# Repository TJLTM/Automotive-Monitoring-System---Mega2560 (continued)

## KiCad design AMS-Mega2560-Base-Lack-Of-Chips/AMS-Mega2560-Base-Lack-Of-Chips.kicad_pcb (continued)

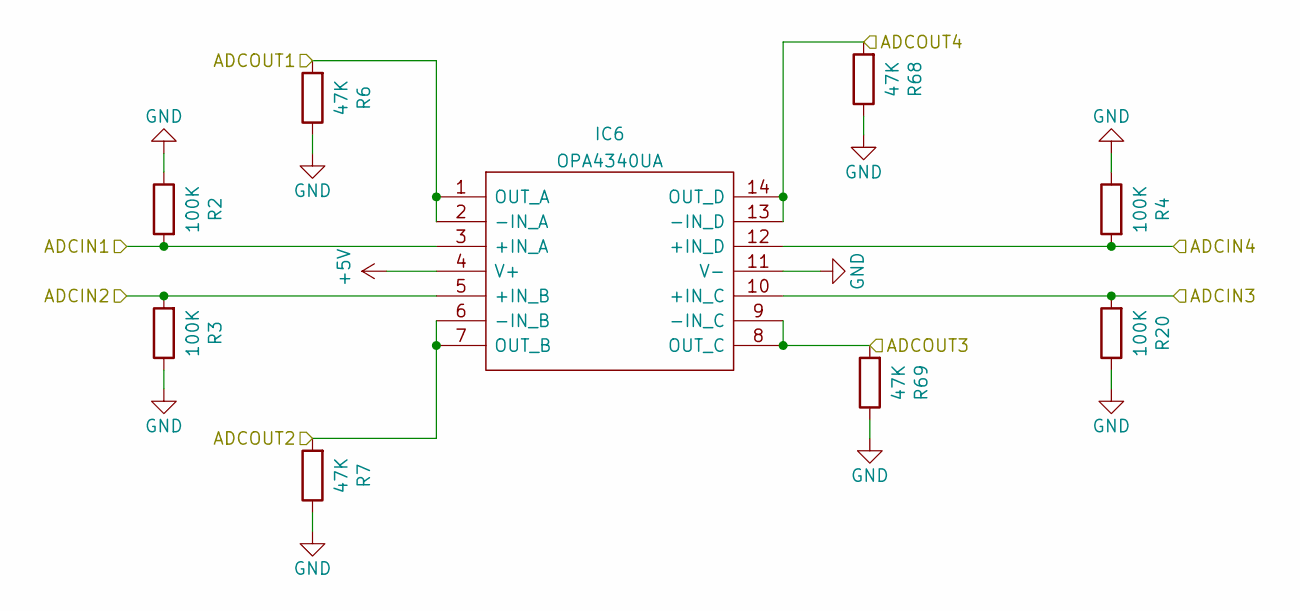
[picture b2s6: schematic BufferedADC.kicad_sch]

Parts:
IC6: OPA4340UA; SOIC127P600X175-14N; Mouser Part Number 595-OPA4340UA
R2, R3, R4, R20: 100K; R_Axial_DIN0207_L6.3mm_D2.5mm_P2.54mm_Vertical
R6, R7, R68, R69: 47K; R_Axial_DIN0207_L6.3mm_D2.5mm_P2.54mm_Vertical

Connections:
AFR1: IC6.6 (-IN_B), IC6.7 (OUT_B), R7.2; also elsewhere on the board
AFR2: IC6.8 (OUT_C), IC6.9 (-IN_C), R69.2; also elsewhere on the board
AltCurrent: IC6.13 (-IN_D), IC6.14 (OUT_D), R68.2; also elsewhere on the board
OilPressure: IC6.1 (OUT_A), IC6.2 (-IN_A), R6.2; also elsewhere on the board

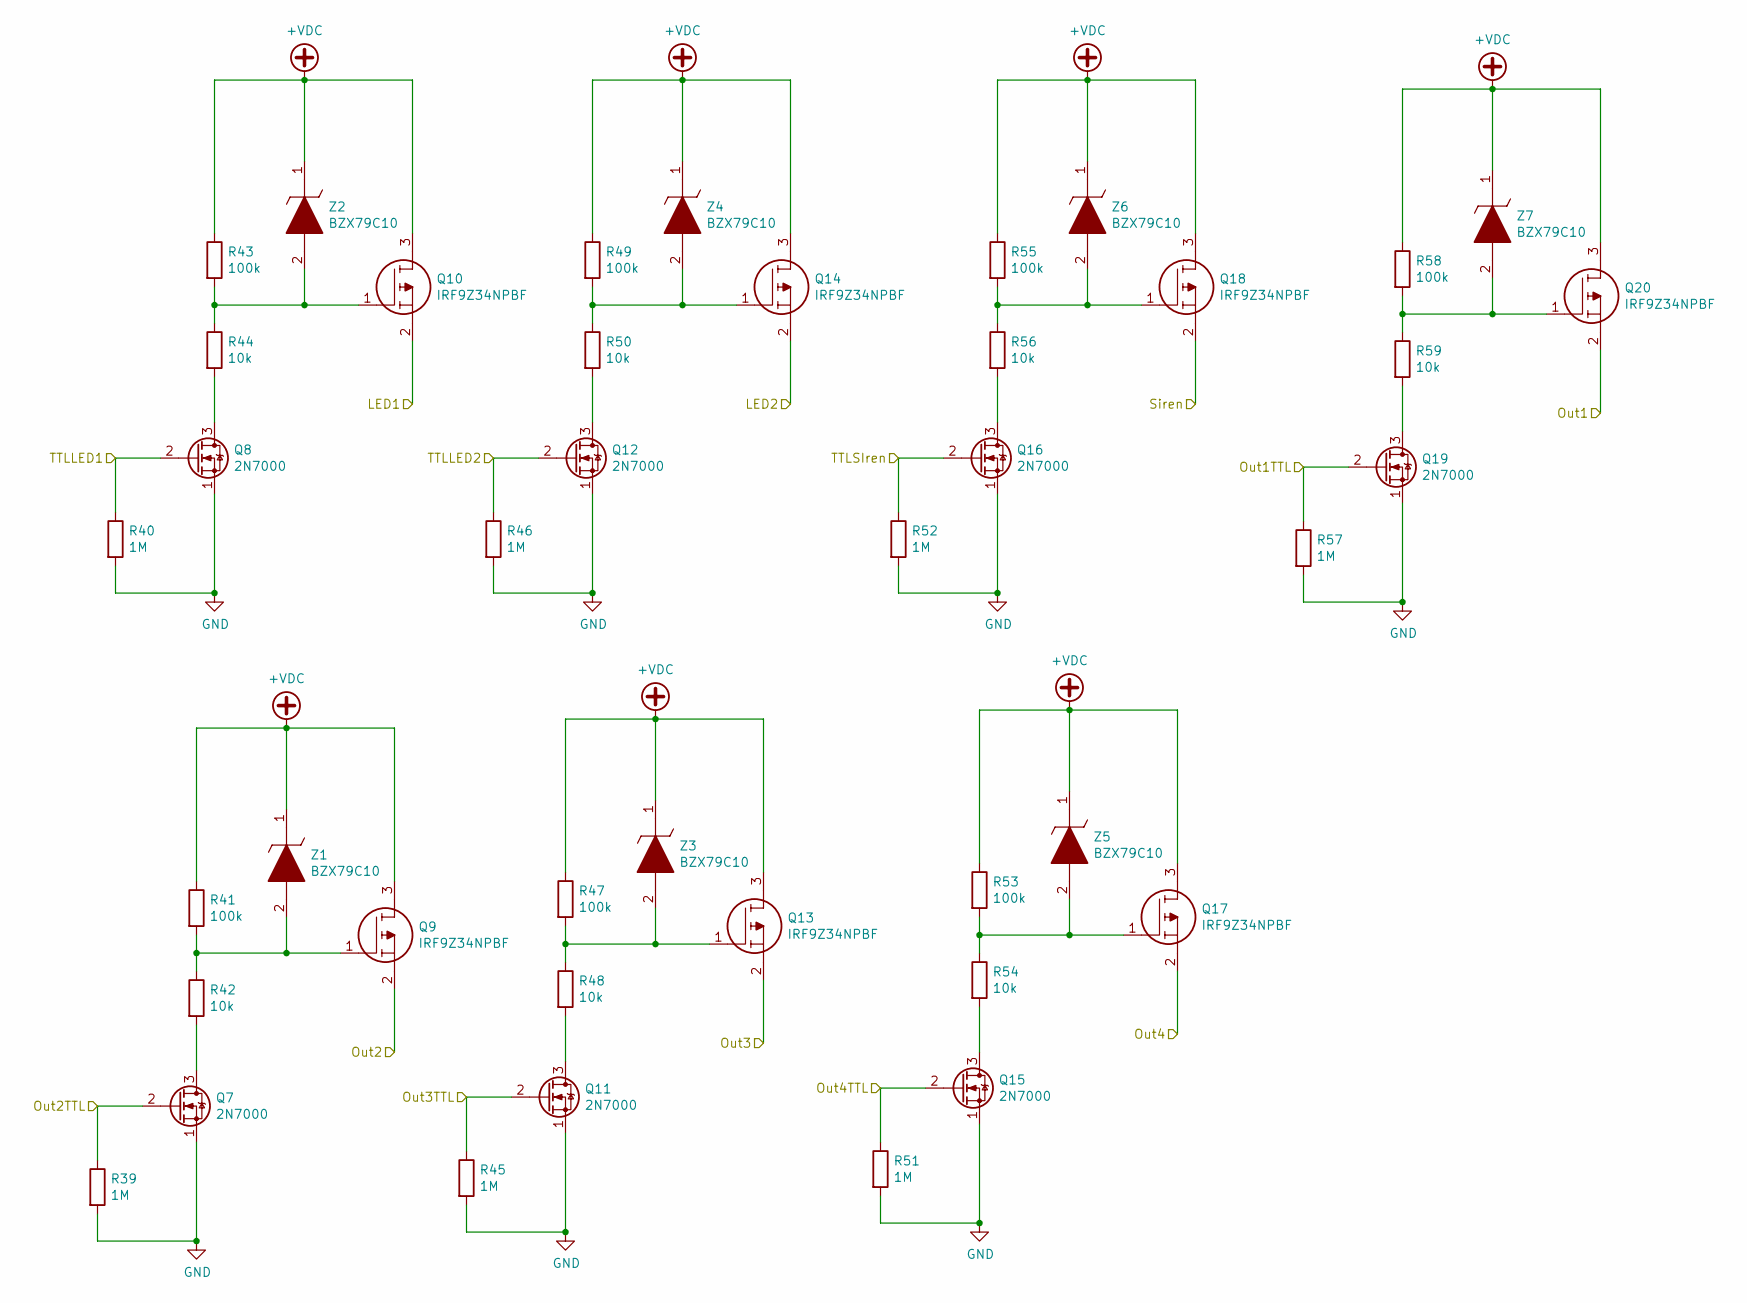
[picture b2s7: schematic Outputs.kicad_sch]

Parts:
Q7, Q8, Q11, Q12, Q15, Q16, Q19: 2N7000; TO-92_Inline
Q9, Q10, Q13, Q14, Q17, Q18, Q20: IRF9Z34NPBF; TO254P469X1042X1967-3P; Mouser Part Number 942-IRF9Z34NPBF
R39, R40, R45, R46, R51, R52, R57: 1M; R_Axial_DIN0207_L6.3mm_D2.5mm_P2.54mm_Vertical
R41, R43, R47, R49, R53, R55, R58: 100k; R_Axial_DIN0207_L6.3mm_D2.5mm_P2.54mm_Vertical
R42, R44, R48, R50, R54, R56, R59: 10k; R_Axial_DIN0207_L6.3mm_D2.5mm_P2.54mm_Vertical
Z1, Z2, Z3, Z4, Z5, Z6, Z7: BZX79C10; DIOAD1068W53L380D172; Mouser Part Number 512-BZX79C10

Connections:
+VDC: Q9.3, Q10.3, Q13.3, Q14.3, Q17.3, Q18.3, Q20.3, R41.1, R43.1, R47.1, R49.1, R53.1, R55.1, R58.1, Z1.1, Z2.1, Z3.1, Z4.1, Z5.1, Z6.1, Z7.1; also elsewhere on the board
unnamed: Q7.3 (D), R42.2
unnamed: Q8.3 (D), R44.2
unnamed: Q9.1, R41.2, R42.1, Z1.2
unnamed: Q10.1, R43.2, R44.1, Z2.2
unnamed: Q11.3 (D), R48.2
unnamed: Q12.3 (D), R50.2
unnamed: Q13.1, R47.2, R48.1, Z3.2
unnamed: Q14.1, R49.2, R50.1, Z4.2
unnamed: Q15.3 (D), R54.2
unnamed: Q16.3 (D), R56.2
unnamed: Q17.1, R53.2, R54.1, Z5.2
unnamed: Q18.1, R55.2, R56.1, Z6.2
unnamed: Q19.3 (D), R59.2
unnamed: Q20.1, R58.2, R59.1, Z7.2
OUTPUT1: Q19.2 (G), R57.1; also elsewhere on the board
OUTPUT2: Q7.2 (G), R39.1; also elsewhere on the board
OUTPUT3: Q11.2 (G), R45.1; also elsewhere on the board
OUTPUT4: Q15.2 (G), R51.1; also elsewhere on the board
OUTPUTLED1: Q8.2 (G), R40.1; also elsewhere on the board
OUTPUTLED2: Q12.2 (G), R46.1; also elsewhere on the board
OUTPUTSiren: Q16.2 (G), R52.1; also elsewhere on the board
Sense2-3: Q20.2; also elsewhere on the board
Sense2-5: Q18.2; also elsewhere on the board
Sense2-6: Q9.2; also elsewhere on the board
Sense2-8: Q14.2; also elsewhere on the board
Sense2-9: Q13.2; also elsewhere on the board
Sense2-11: Q10.2; also elsewhere on the board
Sense2-12: Q17.2; also elsewhere on the board

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
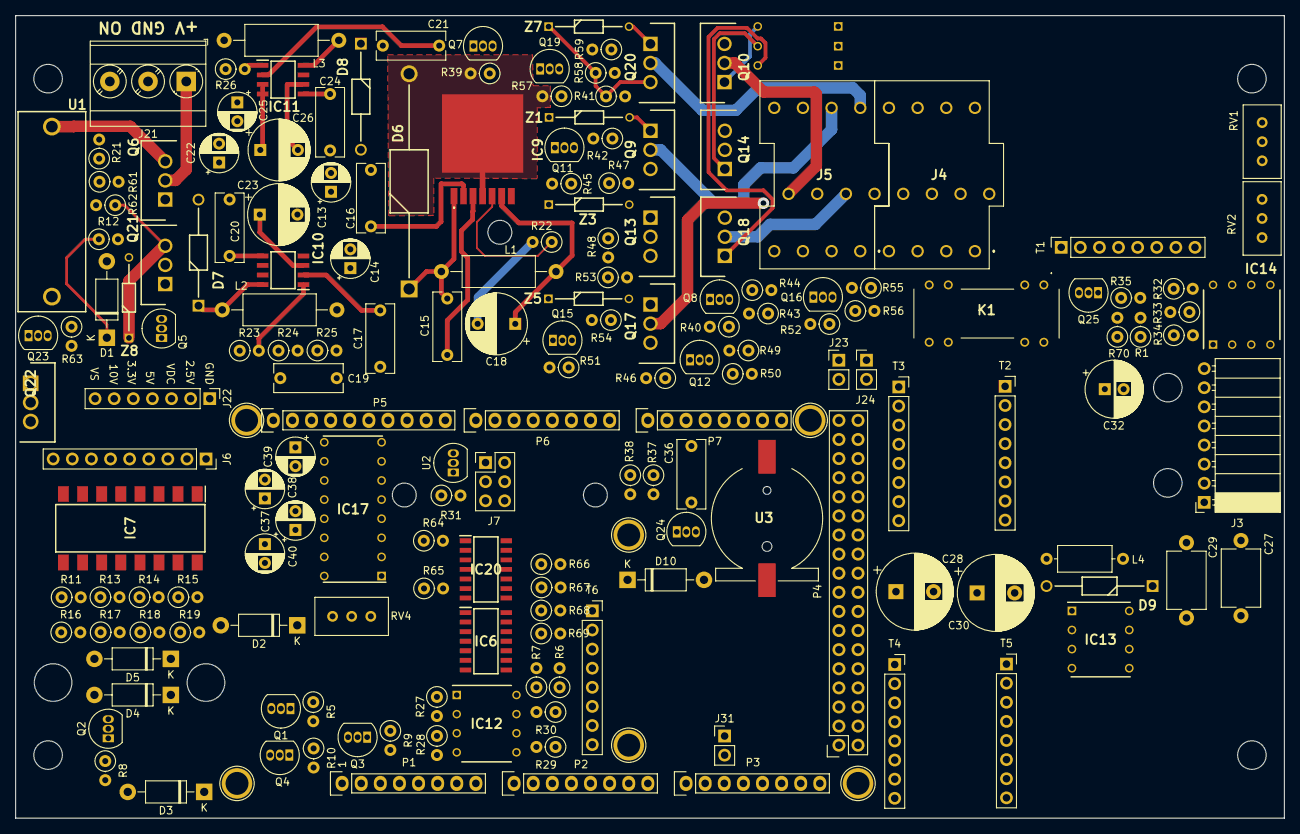
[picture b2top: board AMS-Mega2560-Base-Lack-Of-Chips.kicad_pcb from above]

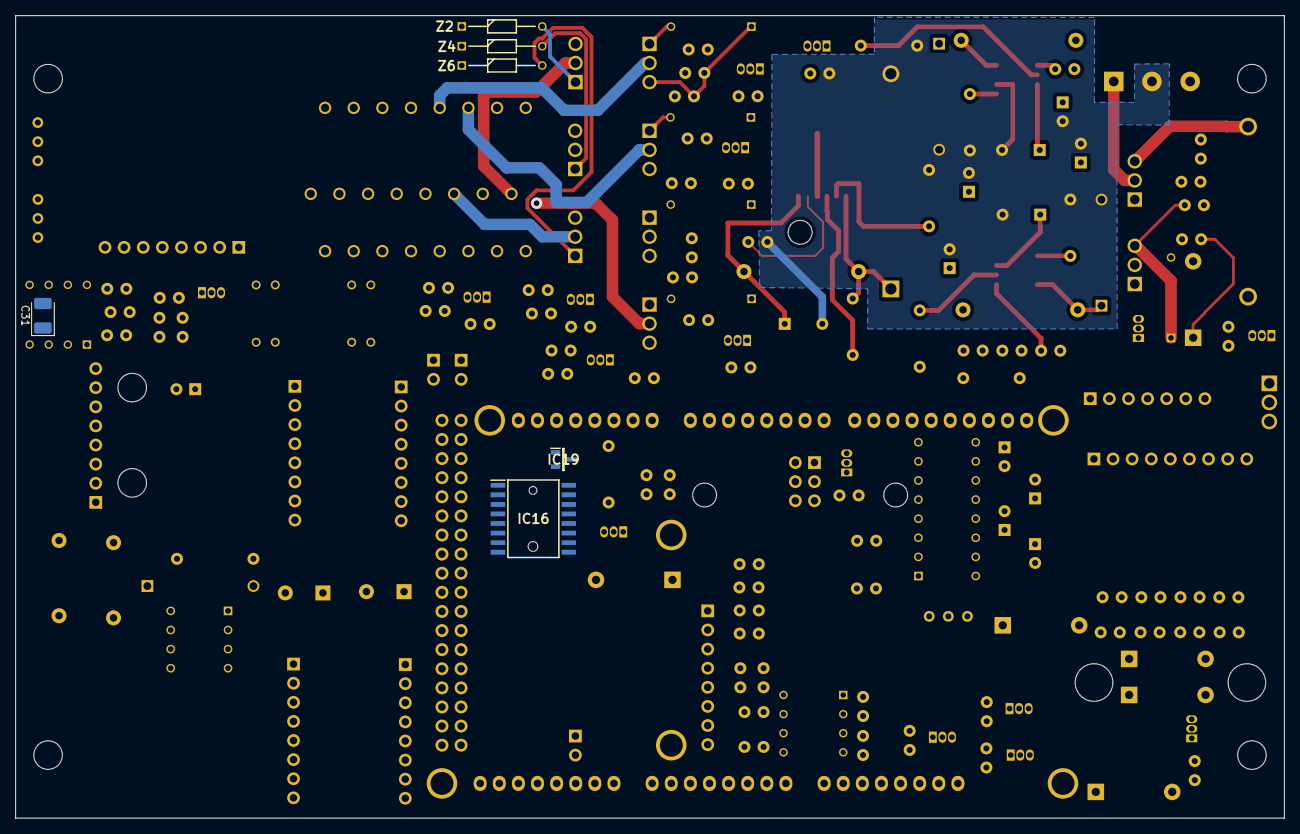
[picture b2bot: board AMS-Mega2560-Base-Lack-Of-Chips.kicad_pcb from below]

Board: 4 copper layers, 168.7 x 106.7 mm, 184 parts (6 on the bottom side), 141 nets.

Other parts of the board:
C36: 0.1uF; C_Rect_L9.0mm_W3.6mm_P7.50mm_MKT
D10: 1N4001; D_DO-41_SOD81_P10.16mm_Horizontal
IC16: DS3231SN#; SOIC127P1032X265-16N
IC19: MAX6326UR31+T; SOT95P237X112-3N
IC20: OPA4340UA; SOIC127P600X175-14N
Q24: BS250; TO-92_Inline
R37, R38: 10k; R_Axial_DIN0207_L6.3mm_D2.5mm_P2.54mm_Vertical
R64, R65, R66, R67: 47K; R_Axial_DIN0207_L6.3mm_D2.5mm_P2.54mm_Vertical
U3: S8411-45R; S8411-45R_1

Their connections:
/A1: Q24.1 (D), U3.1 (+); also elsewhere on the board
/BufferedADC/ADCIN4: IC20.12 (+IN_D); also elsewhere on the board
FuelPressure1: IC20.1 (OUT_A), IC20.2 (-IN_A), R64.2; also elsewhere on the board
FuelPressure2: IC20.6 (-IN_B), IC20.7 (OUT_B), R65.2; also elsewhere on the board
unnamed: D10.1 (K), IC16.14 (VBAT), Q24.3 (S)
unnamed: IC19.2 (~RESET), Q24.2 (G)
SCL: IC16.16 (SCL), R37.2; also elsewhere on the board
SDA: IC16.15 (SDA), R38.2; also elsewhere on the board
Sense1-6: IC20.10 (+IN_C); also elsewhere on the board
Sense1-9: IC20.5 (+IN_B); also elsewhere on the board
Sense1-12: IC20.3 (+IN_A); also elsewhere on the board
SpareBufferedADC: IC20.13 (-IN_D), IC20.14 (OUT_D), R66.2; also elsewhere on the board
ThrottlePositionADC: IC20.8 (OUT_C), IC20.9 (-IN_C), R67.2; also elsewhere on the board

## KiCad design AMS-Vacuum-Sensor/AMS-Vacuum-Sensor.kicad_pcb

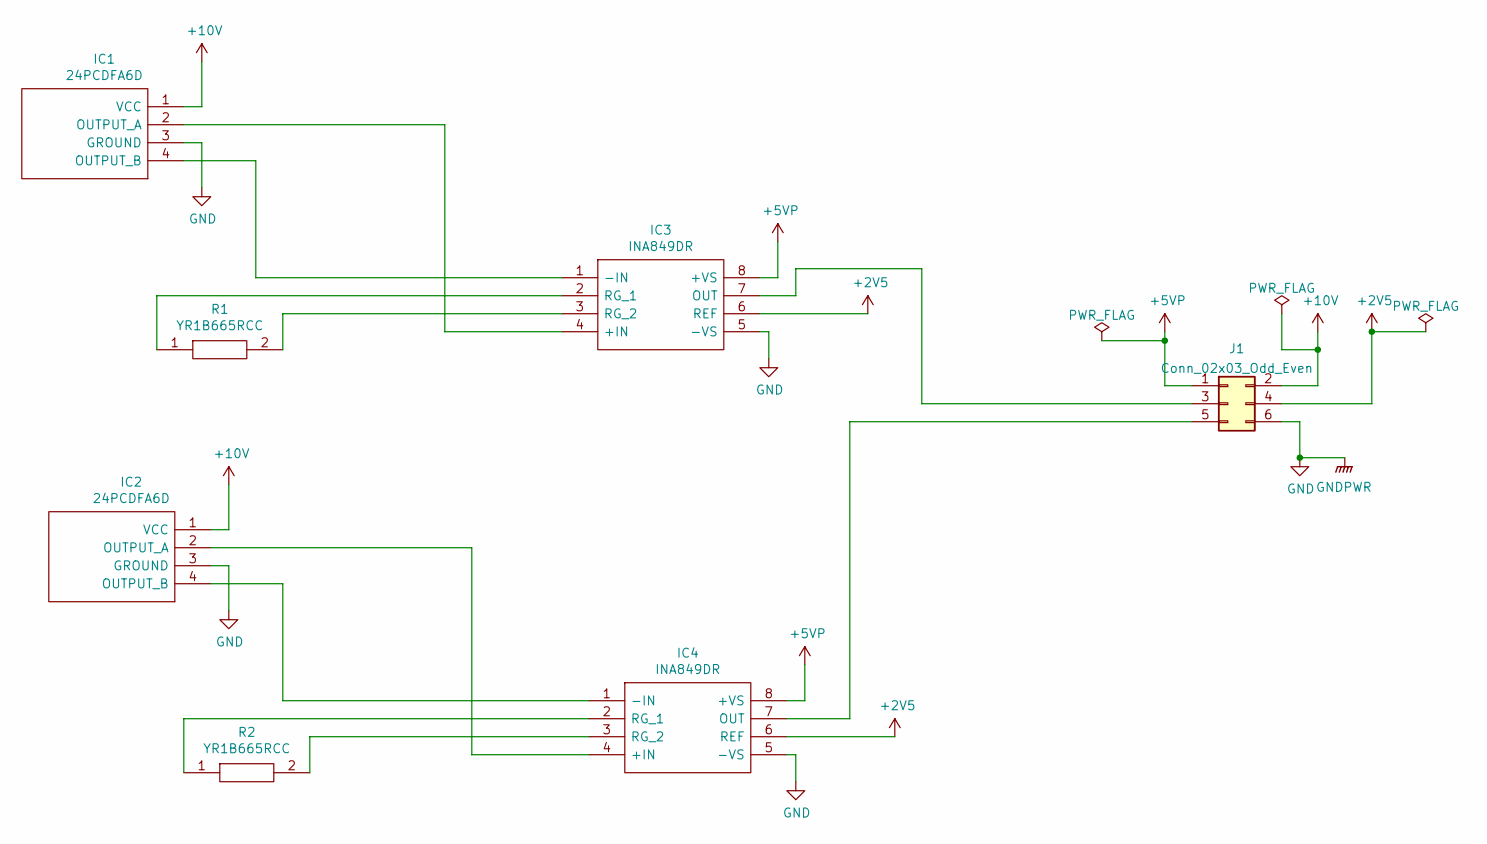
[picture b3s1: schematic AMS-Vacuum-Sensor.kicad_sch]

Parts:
IC1, IC2: 24PCDFA6D; Mouser Part Number 785-24PCDFA6D
IC3, IC4: INA849DR; SOIC127P600X175-8N; Mouser Part Number 595-INA849DR
J1: Conn_02x03_Odd_Even; PinHeader_2x03_P2.54mm_Vertical
R1, R2: YR1B665RCC; RESAD1550W60L630D230; Mouser Part Number 279-YR1B665RCC

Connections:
+2V5: IC3.6 (REF), IC4.6 (REF), J1.4
+5VP: IC3.8 (+VS), IC4.8 (+VS), J1.1
+10V: IC1.1 (VCC), IC2.1 (VCC), J1.2
GND: IC1.3 (GROUND), IC2.3 (GROUND), IC3.5 (-VS), IC4.5 (-VS), J1.6
unnamed: IC1.2 (OUTPUT_A), IC3.4 (+IN)
unnamed: IC1.4 (OUTPUT_B), IC3.1 (-IN)
unnamed: IC2.2 (OUTPUT_A), IC4.4 (+IN)
unnamed: IC2.4 (OUTPUT_B), IC4.1 (-IN)
unnamed: IC3.2 (RG_1), R1.1
unnamed: IC3.3 (RG_2), R1.2
unnamed: IC3.7 (OUT), J1.3
unnamed: IC4.2 (RG_1), R2.1
unnamed: IC4.3 (RG_2), R2.2
unnamed: IC4.7 (OUT), J1.5

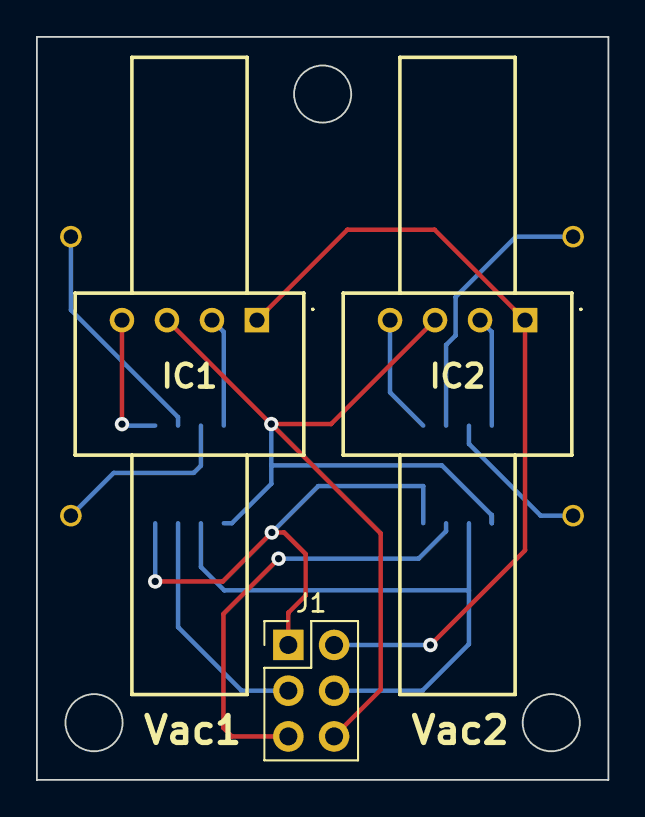
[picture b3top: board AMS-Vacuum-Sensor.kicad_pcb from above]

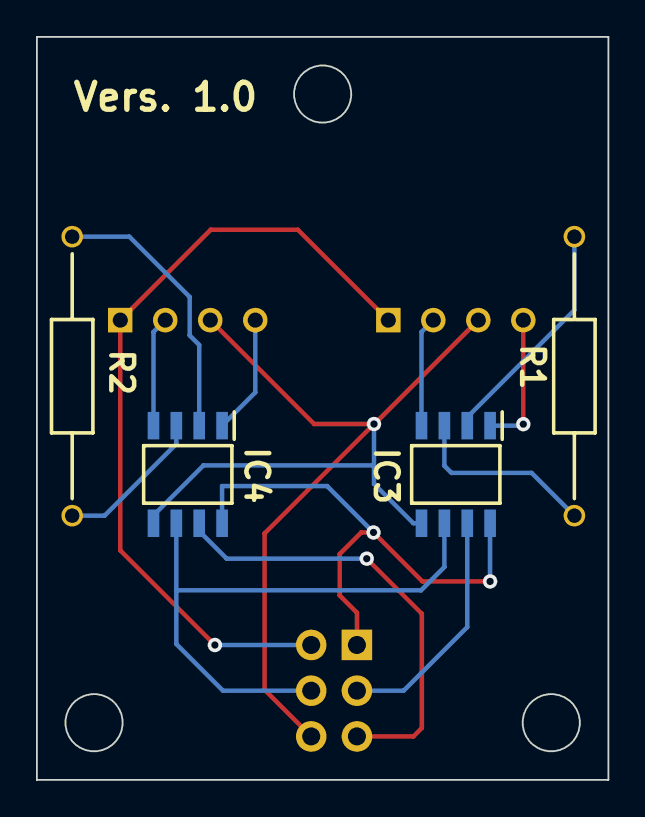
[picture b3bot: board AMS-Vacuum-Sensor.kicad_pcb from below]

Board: 2 copper layers, 31.8 x 41.3 mm, 7 parts (4 on the bottom side), 14 nets.

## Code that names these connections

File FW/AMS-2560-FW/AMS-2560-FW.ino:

#include <LiquidCrystal_I2C.h>
#include <Wire.h>
#include <Adafruit_MAX31865.h>
#include <SPI.h>
#include <RTClib.h>
#include <EEPROM.h>

//-----------------------------------------------------------
// Serial Communication, UI 
//-----------------------------------------------------------
#define USBSerial Serial
#define RS232 Serial2
#define GPSSerial Serial3
String inputString, inputStringRS232 = "";         // a String to hold incoming data from ports
bool stringComplete, stringCompleteRS232 = false;     // whether the string is complete for each respective port

char* AcceptedCommands[] = {"UNITS?", "DEVICE?", "BATTERY?", "RTCBATTERY?", "TEMPS?", "UNITTEMP?", "WARNING?",
                            "STREAMING?", "ALLDATA?", "UPDATEALL", "RESETWARNINGS", "RESETALLALARMS",
                            "TIME?", "REBOOT", "RESET", "STREAMINGONBOOT?"
                           };
char* ParameterCommands[] = {"SETUNITS", "SETSTREAMINGDATA", "SETOUTPUT", "READINPUT", "SETTIME", "GETOUTPUT", "READANALOG", 
                             "SETSTREAMINGONBOOT"
                            };

//-----------------------------------------------------------
// System Level
RTC_DS3231 rtc;
const String DeviceName = "AMS";
const String FWVersion = "1.0.0";
const float ConversionFactor = 5.0 / 1023;

char Units;
String TempUnits, PressureUnits;
const String StatesForOutput[2] = {"Off", "On"};

//-----------------------------------------------------------
//-----------------------------------------------------------
//Spare IO
/*
   Spare Inputs are indexed by their number +1 because I don't
   want to start at zero.
*/
const int SpareInputs[] = {2,3,47};
const int SpareInputSize = sizeof(SpareInputs) / sizeof(int);
int LastInputState[] = {};
const int SpareOutputs[] = {4,5,6,7};
const int SpareOutputSize = sizeof(SpareOutputs) / sizeof(int);
//-----------------------------------------------------------
//-----------------------------------------------------------
//Analog Sensors 
#define VoltageSensor A0
#define RTCBattery A1
#define Vacuum1 A2
#define Vacuum A3
#define AtlernatorCurrent A4
#define FuelPresssure1 A5
#define FuelPressure2 A6
#define AFR1 A8
#define AFR2 A9
#define RPM A10
#define GPSBattery A11
#define ThrottlePosition A12
#define SpareBufferedADC A13
//-----------------------------------------------------------
//-----------------------------------------------------------
//Specific IO 
#define OutputSiren 10
#define LED1 43
#define LED2 45
#define LoggingIn 49
#define SDCardDetect 34
//-----------------------------------------------------------
//-----------------------------------------------------------
//RTD 
#define RREF 430.0
#define RNOMINAL 100.0
#define RTDCLK 44
#define RTDDI 48
#define RTDDO 46
Adafruit_MAX31865 Water = Adafruit_MAX31865(48, RTDDI, RTDDO, RTDCLK);
Adafruit_MAX31865 LeftSide = Adafruit_MAX31865(46, RTDDI, RTDDO, RTDCLK);
Adafruit_MAX31865 RightSide = Adafruit_MAX31865(44, RTDDI, RTDDO, RTDCLK);
Adafruit_MAX31865 Carb = Adafruit_MAX31865(38, RTDDI, RTDDO, RTDCLK);
Adafruit_MAX31865 FrontOfEngine = Adafruit_MAX31865(42, RTDDI, RTDDO, RTDCLK);
Adafruit_MAX31865 Ambient = Adafruit_MAX31865(40, RTDDI, RTDDO, RTDCLK);
//-----------------------------------------------------------
//-----------------------------------------------------------
/*
   All the Stored Values and Times to have states
   that can be recalled if streaming is turned off
*/
//Energy Monitoring
float LastDCVoltage, LastAltCurrent, LastRTCVoltage = 0.0;
String LastTimeDCVoltage, LastTimeRTCVoltage = "";
//Temps
String LastTimeTemp = "";
float LastFrontACTemp, LastBackACTemp, LastOutsideTemp, LastBackCabinTemp, LastHallwayTemp, LastFreezerTemp, LastFridgeTemp,
      LastBathroomTemp = 0.0;
//RTC TEMP
float LastRTCTemp = 0.0;
String LastTimeRTCTemp = "";
//-----------------------------------------------------------
//-----------------------------------------------------------

void setup() {
  rtc.begin();
  RS232.begin(115200);
  USBSerial.begin(115200);
  inputString.reserve(200);
  inputStringRS232.reserve(200);

  for (int i = 0; i <= SpareInputSize; i++) {
    pinMode(SpareInputs[i], INPUT);
    LastInputState[i] = digitalRead(SpareInputs[i]);
  }
  for (int i = 0; i <= SpareOutputSize; i++) {
    pinMode(SpareOutputs[i], OUTPUT);
  }

}

void loop() {
  

}


//------------------------------------------------------------------
//Helper functions
//------------------------------------------------------------------
void(* resetFunc) (void) = 0;  // declare reset fuction at address 0

void RebootDisBitch() {
  BroadCast("%R," + GetCurrentTime() + ",Rebooting");
  delay(2000);
  resetFunc();
}

void MIBFLASH() {
  BroadCast("%R," + GetCurrentTime() + ",Reseting wait for reboot Message");
  for (int i = 0 ; i < EEPROM.length() ; i++) {
    EEPROM.write(i, 0);
  }
  RebootDisBitch();
}

float ConvertCtoF(float C) {
  float F = (1.8 * C) + 32;
  return F;
}

float ConvertPSItoKPa(float PSI) {
  float KPA = 6.8947572932 * PSI;
  return KPA;
}

String GetCurrentTime() {
  DateTime now = rtc.now();

  char buf1[20];
  sprintf(buf1, "%02d:%02d:%02d-%02d/%02d/%02d",  now.hour(), now.minute(), now.second(), now.day(), now.month(), now.year());
  LastTimeRTCTemp = buf1;
  
  if (Units == 'I') {
    LastRTCTemp = ConvertCtoF(rtc.getTemperature());
  }
  else {
    LastRTCTemp = rtc.getTemperature();
  }
  return DateTimeString;
}

String GetCurrentDate() {
  DateTime now = rtc.now();
  String CurrentDate = String(now.year()) + String(now.month()) + String(now.day());
  return CurrentDate;
}

void SetUnitsForOutput() {
  if (Units == "M") {
    TempUnits = "C";
    PressureUnits = "KPa";
  }
  else {
    TempUnits = "F";
    PressureUnits = "PSI";
  }
}

void ReadAllInputs() {
  for (int i = 1; i <= SpareInputSize; i++) {
    int CurrentInputRead = ReadInput(SpareInputs[i]);
    if (CurrentInputRead != LastInputState[i]) {
      LastInputState[i] = CurrentInputRead;
      if (StreamingDataUSB == true) {
        PrintInputState(i, CurrentInputRead, 0);
      }
      if (StreamingDataRS232 == true) {
        PrintInputState(i, CurrentInputRead, 1);
      }

    }
  }
}

int ReadInput(int Number) {
  int Value = digitalRead(SpareInputs[Number]);
  return Value;
}

int ReadOutput(int Number) {
  int Value = digitalRead(SpareOutputs[Number - 1]);
  return Value;
}

float ReadAnalog(int Samples, int PinNumber) {
  long Sum = 0;
  float Value = 0;
  for (int x = 0; x < Samples; x++) {
    Sum = Sum + analogRead(PinNumber);
  }
  Value = (Sum / Samples);
  return Value;
}


//------------------------------------------------------------------
//Serial
//------------------------------------------------------------------
/*
  SerialEvent occurs whenever a new data comes in the hardware serial RX. This
  routine is run between each time loop() runs, so using delay inside loop can
  delay response. Multiple bytes of data may be available.
*/
void serialEvent() {
  while (USBSerial.available()) {
    // get the new byte:
    char inChar = (char)USBSerial.read();
    // add it to the inputString:
    inputString += inChar;
    // if the incoming character is a carriage return, set a flag so the main loop can
    // do something about it:
    if (inChar == '\r') {
      stringComplete = true;
    }
  }
}

void serialRS232() {
  while (RS232.available()) {
    // get the new byte:
    char inChar = (char)RS232.read();
    // add it to the inputString:
    inputStringRS232 += inChar;
    // if the incoming character is a carriage return, set a flag so the main loop can
    // do something about it:
    if (inChar == '\r') {
      stringCompleteRS232 = true;
    }
  }
}

void BroadCast(String Message) {
  SendItOut(Message, 0);
  SendItOut(Message, 1);
}

void SendItOut(String Message, int WhichPort) {
  if (WhichPort == 0) {
    USBSerial.println(Message);
  }
  else {
    RS232.println(Message);
  }
}

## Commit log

2021-08-16 initial blank kicad project
2021-09-22 mostly done. I need to double check the SDcard circuit design and verify that it will work. also i need to route to the term blocks for the RTDs
2021-09-26 fixing some fuck ups in the hierarchical sheets and deleted some unused ref
2021-09-26 still fixing the schematic the coms/RTC need to assign footprints and double check all the parts in that file.
2021-09-26 fixed the schematics for the RTC, IO and COMs. Realigned the RTD to screw term. need to finish the 3.3v portion of the power systems.
2021-10-05 wip working on it.
2021-10-08 rearranging some of the hw design before i rename the repo.
2022-01-07 upgrading this to 6.0 and moving the vacuum sensors to a daughter board project.
2022-01-07 fixing some library settings and updating some schematics
2022-01-09 BaseBoard fixes and updates. doing schematic work.
2022-01-10 trying to fix the PCB layout.
2022-01-10 rollback and file clean up.
2022-01-10 fixed the messed up references and cleaned up the schematic.
2022-01-11 working on pcb layout
2022-01-12 wip for the base PCB, finished Vacuum PCB and Fab Files for that.
2022-01-14 WIP for layout
2022-01-15 moving the Vacuum sensor daughter board to the vacuum sensor project.
2022-02-01 wip adding the throttle position sensor input stuff.
2022-02-05 slowly working on getting the board laid out and updates to some of the schematics.
2022-02-07 WIP for layout.
2022-02-07 continuing pcb layout
2022-02-08 I think everything is placed on the board special routes have been done. need to finish routing everything else.
2022-02-13 WIP for power on input and RTC battery switch over.
2022-02-14 moving some things around on the board to clear the Vacuum board.
2022-02-22 fixing the 5V lines and removing the 5V fromt he MCU board and only using the 3Amp 5v power supplied by CampKeen
2022-02-22 working on ERC
2022-02-22 still fixing ERC stuff
2022-02-22 cleared all of the ERC stuff need to go over some of the power stuff for this before finishing routing.
2022-02-22 Schematic ERC is done and DRC for current layout is done. Need to verify a new part of the circuit before routing the rest of the board.
2022-02-22 adding initial FW sketch.
2022-02-23 pushing this change to the repo need to vet some schematics
2022-02-24 adding some fixes for the RPM sensor and trying to fit everything on the board. WIp for FW
2022-02-25 adding the buffered adcs to this. before splitting the project due to lack of chips.
2022-02-25 adding lack of chips project where i have to replace the RTD with Dev boards
2022-02-25 replaced the RTD with adafruit Dev boards which are easy to get at the moment.
2022-02-27 updating some Resistor values
2022-02-28 removing this as it's not needed in this design anymore
2022-02-28 removing separate project for lack of chips and switching to dev boards. copied out the schematics used.
2022-02-28 orphaned sheets until a can get the correct chips
2022-03-23 applying some fixes for the RPM sensor and other parts of the schem
2022-03-28 updated a few things for the SPI lines to the RTDs ready for routing.
2022-03-31 routed needs to get all DRC'ed.
2022-04-06 routed and DRC'ed. almost ready to send off to be Fabbed.
2022-04-27 adding HTML BOM
2022-04-28 made dem fab files.
2022-04-30 Update AMS-2560-FW.ino
    changing the date string to be a sprintf instead of string stuff.
2022-05-01 moving some files around for orgizational stuff. adding hw verification stuff just copied over my base fw frame work. which is a bang to fit paint to match campkeen since they kind of have to do the 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
2022-05-18 wip trying to get this framework there for testing.
2022-05-29 updated SD Card Detect resistor to be 47k vs 50k
2022-06-01 updating some values and footprints. needs to have the routing tweaked
2022-06-03 working on getting the verification code done
2022-06-03 think this is done needs to be tested out.
2022-06-23 replacing all the old code with this from CampKeen. the frame work is there but i need to remove all the CampKeeness and properly setup the pins and some of the other stuff.
2022-06-24 working on fixing the screw ups. adding a second serial port
2022-06-27 still working on the base code. updating some of the HW stuff
2022-07-03 fixing software SPI
2022-07-04 working on the verification code while i test what is f-ing wrong with this hardware
2022-07-05 cleaning up and adding to the verification program
2022-07-05 merging something from last night.
2022-07-05 fixed all the bad merges.
2022-07-06 updating some pin defs
2022-07-06 * Swapped RX/TX for the GPS * added pull down resistors on buffered ADCs * Removed pot on SpareBufferedADC
2022-07-06 adding to RPM reading.
2022-07-07 saving this here.
2022-07-08 updating this for the merge.
2022-07-08 removing the GPS libs as they aren't needed for this and adding in the rs232 testing.
2022-07-09 wip for adding second rs232 port. needs to have the other end added to an output pin/port
2022-07-13 still working on the fixes.
2022-07-14 just need to route the 5V power around the board before i figure out what to do with the other serial port
2022-07-15 wip while i get set to autoroute
2022-07-15 fixed 2.5v source. added gnd fill area to keep the noise down.
2022-07-15 ready to autoroute
2022-07-15 autorouted needs to be DRC'ed and fix whatever the autorouter did horribly
2022-07-16 finished routing and DRC. Generated FabFiles
2022-07-17 changing SMD footprint for RPM sensor CAP reDRC'ed and remade the FAB files
2022-07-17 pushing Fab Files
2022-07-28 updating the bom
2022-08-10 fixed footprint and synced schem and layout
2022-10-13 updating the inputs and reannotating some stuff.
2023-05-02 not sure what i changed i'm pushing these up since this branch may be deleted
2023-06-04 working on this.
2023-06-11 finished CAN section. inputs need to be fixed.
2023-07-14 * Schematic ** finished CAN bus Design work ** updated the input circuits to my standard design and removed the old one that was funky
    * PCB
    ** updated footprints
    ** removed the old parts/designed
    ** starting prep for placing parts
2023-07-31 * got parts placed * modified the Input circuit design to include Nchannel fet Needs the tricky routes done before doing autoroute
2023-08-01 added I2C pullup resistors DRCed and fixed everything Pre Routing. Routed some of the basics. all parts are placed on the board. Pre Autoreouting.
2023-08-01 Fab Files updated Added PCBway Zip updating ibom.html Sending this off to Fab.
2023-08-03 fixed the hardware verification stuff. working on updating the FW for this since it's a mismash of CampKeen and The OG AMS
